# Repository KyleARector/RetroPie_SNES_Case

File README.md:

# SNES RetroPie Case

### BOM and Instructions to come...

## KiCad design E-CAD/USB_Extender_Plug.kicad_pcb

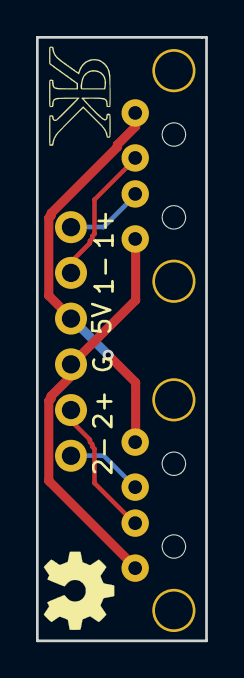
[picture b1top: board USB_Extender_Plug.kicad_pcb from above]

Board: 2 copper layers, 9.4 x 33.5 mm, 3 parts (0 on the bottom side), 6 nets.

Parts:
J1, J2: USB_A; USB_A_Plug
J3: CONN_01X06; USB_Extender_2_Port

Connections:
unnamed: J1.1, J2.1, J3.3
unnamed: J1.2, J3.2
unnamed: J1.3, J3.1
unnamed: J1.4, J2.4, J3.4
unnamed: J2.2, J3.6
unnamed: J2.3, J3.5

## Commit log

2017-08-25 Initial commit of CAD, Electrical CAD, and Python code
2017-09-04 Updating power switch code
